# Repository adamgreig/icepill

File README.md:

# iCE Pill

Breakout board for iCE40UP5k with the STM32F411 "Black Pill" board.

This board breaks all the iCE40UP5k GPIO to PMOD headers, most of which are
also connected to Black Pill pins, allowing either the STM32 or the iCE40 to
drive each PMOD pin. The iCE40's SPI and configuration pins are connected to
the Black Pill, allowing the STM32 to program and control the iCE40.

The SPI and configuration pins are also exposed on the J8 and J9 pin headers,
allowing connection just to these signals and then all PMOD pins can be
exclusively used by the iCE40.

Two additional STM32 pins can be connected to the iCE40: PA8, which can be used
in its MCO or TIM1 CH1 alternate modes to generate a clock for the iCE40, and
PB10, which can be used to signal an interrupt from the iCE40. Zero-ohm
resistors are be fitted in R2 and R3 to connect these signals to PMOD pins
as well, and zero-ohm resistors can optionally be fitted in R7 and R8 to
connect PA9 and PB4 from the STM32 to the same PMOD pins. This configuration
means the iCE40 is always connected to PA8 (clock) and PB10 (interrupt), and
either those iCE40 pins can connect to the PMOD _or_ the STM32 pins PA9 and PB4
can connect to the PMOD instead.

R5 and R6 are present in case a 1.2V fixed LDO is not available and you need
to use an adjustable LDO. Otherwise, leave R5 not fitted and use a zero-ohm
resistor for R6 (the default).

The LED D1 is connected to the RGB0 _and_ RGB1 pins on the iCE40 to simplify
routing; it is recommended that only one pin is used at the same time when
driving the LED.

Pin 35 connects to PMOD 7 pin 8; this pin can be a PLL input to the iCE40. If
the PLL is in use at all (whether fed from pin 35 or any other signal), then
pin 35 cannot be used as a regular input.

| PMOD      | iCE40 | STM32 | Notes
|-----------|-------|-------|------
| P1.1      | 12    | PA12  |
| P1.2      | 11    | PA11  |
| P1.3      | 10    | PA10  |
| P1.4      | 9     | PA9   | Used for IRQ with PB10, PA9 disconnected by default
|           |       |       |
| P2.1      | 21    | PB5   |
| P2.2      | 20    | PB4   | Used for CLK with PA8, PB4 disconnected by default
| P2.3      | 19    | PB3   |
| P2.4      | 18    | PA15  |
|           |       |       |
| P3.1      | 28    | PB9   |
| P3.2      | 27    | PB8   |
| P3.3      | 26    | PB7   |
| P3.4      | 25    | PB6   |
|           |       |       |
| P4.1      | 44    | PA1   |
| P4.2      | 43    | PA0   |
| P4.3      | 42    |       |
| P4.4      | 38    | PC13  |
|           |       |       |
| P5.1      | 48    | PA5   |
| P5.2      | 47    | PA4   |
| P5.3      | 46    | PA3   |
| P5.4      | 45    | PA2   |
|           |       |       |
| P6.1      | 6     | PB1   |
| P6.2      | 4     | PB0   |
| P6.3      | 3     | PA7   |
| P6.4      | 2     | PA6   |
|           |       |       |
| P7.1      | 36    |       |
| P7.2      | 34    |       |
| P7.3      | 31    |       |
| P7.4      | 13    |       |
| P7.7      | 37    |       |
| P7.8      | 35    |       | If PLL active, can only be used as PLL input
| P7.9      | 32    |       |
| P7.10     | 23    |       |
|           |       |       |
|           | 14    | PB14  | SPI SO
|           | 15    | PB13  | SPI SCK
|           | 16    | PB12  | SPI CS
|           | 17    | PB15  | SPI SI
|           | 8     | PB2   | iCE40 CRESET
|           |       |       |
|           | 39    |       | LED on iCE40 RGB0 pin
|           | 40    |       | Connected to pin 39

Symbols and footprints copied from [agg-kicad]. This schematic and PCB design
are licensed under the Creative Commons [CC0 public domain dedication]. It is
provided with no warranty.

[agg-kicad]: https://github.com/adamgreig/agg-kicad
[CC0 public domain dedication]: https://creativecommons.org/publicdomain/zero/1.0/

## Revision History

### 1.0: 2020-11-08

* First revision.
* Errata:
    * None yet.

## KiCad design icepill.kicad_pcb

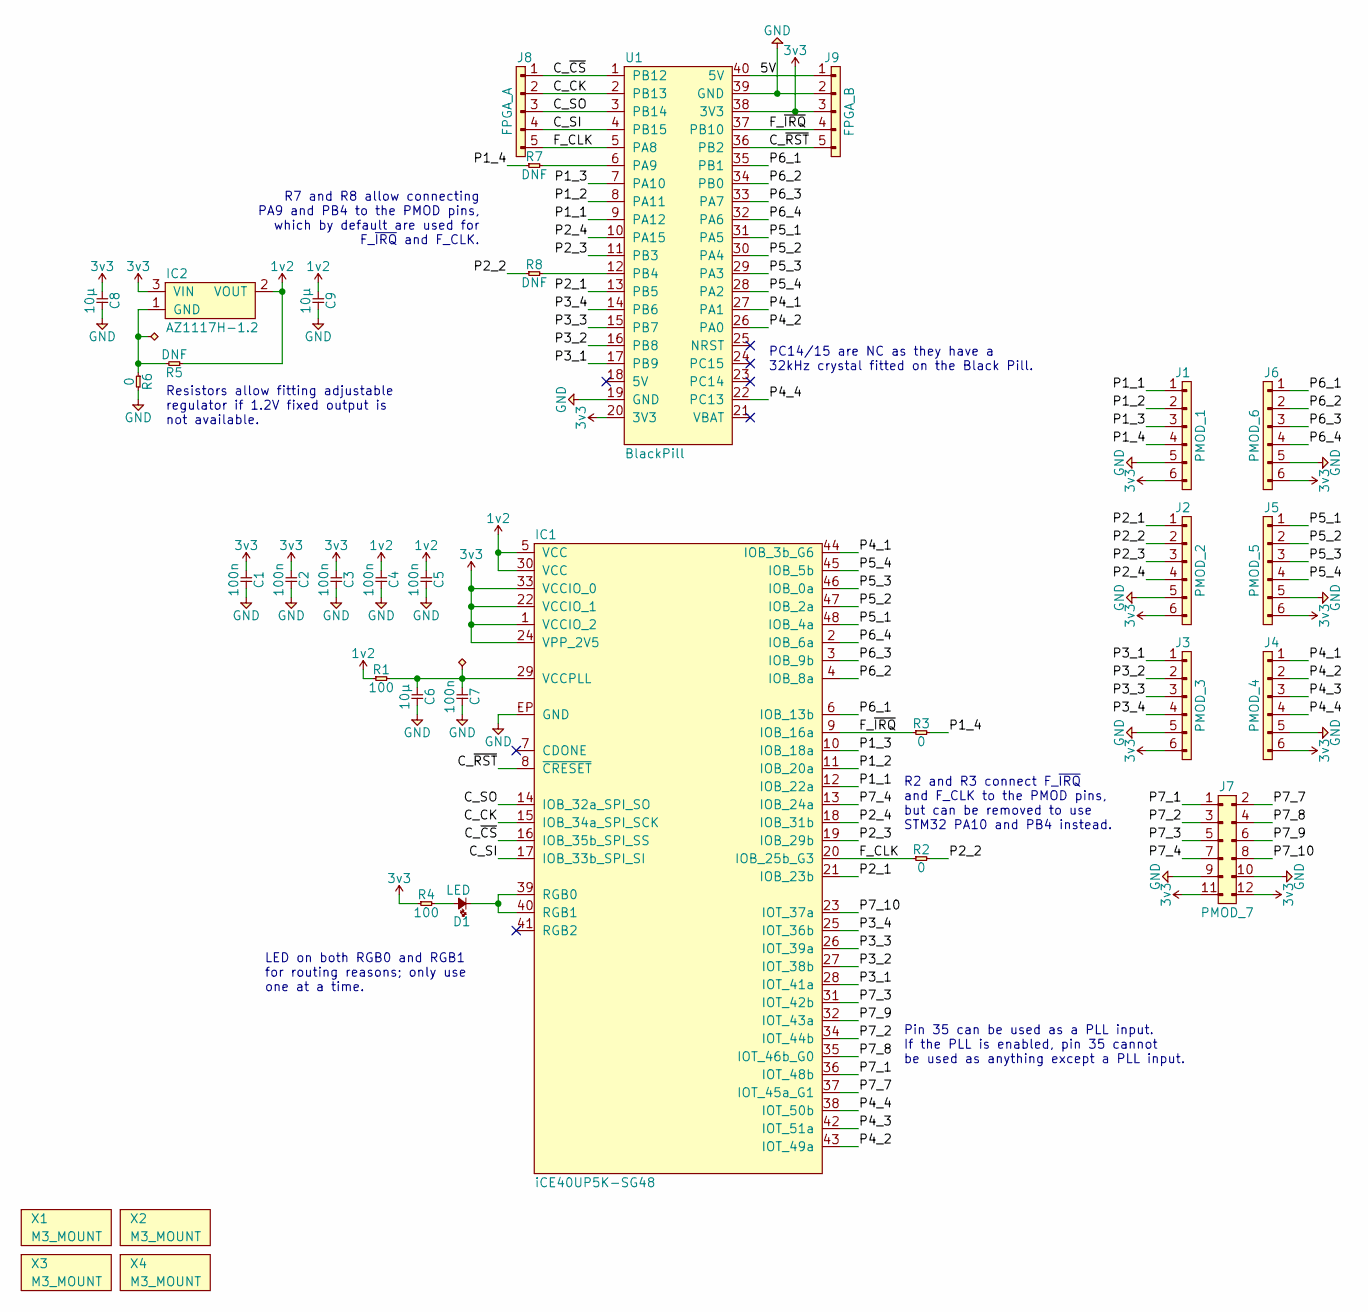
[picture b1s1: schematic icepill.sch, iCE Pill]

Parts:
C1, C2, C3, C4, C5, C7: 100n; 0603; Voltage 10
C6, C8, C9: 10µ; 0805; Voltage 10
D1: LED; 0603-LED
IC1: iCE40UP5K-SG48; Lattice-SG48; DigiKey 220-2212-1-ND
IC2: AZ1117H-1.2; SOT223
J1: PMOD_1; SIL-254P-06
J2: PMOD_2; SIL-254P-06
J3: PMOD_3; SIL-254P-06
J4: PMOD_4; SIL-254P-06
J5: PMOD_5; SIL-254P-06
J6: PMOD_6; SIL-254P-06
J7: PMOD_7; DIL-254P-12
J8: FPGA_A; SIL-254P-05
J9: FPGA_B; SIL-254P-05
R1, R4: 100; 0603
R2, R3, R6: 0; 0603
R5, R7, R8: DNF; 0603
U1: BlackPill
X1, X2, X3, X4: M3_MOUNT

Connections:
1v2: C4.1, C5.1, C9.1, IC1.5 (VCC), IC1.30 (VCC), IC2.2 (VOUT), R1.1, R5.1
3v3: C1.1, C2.1, C3.1, C8.1, IC1.1 (VCCIO_2), IC1.22 (VCCIO_1), IC1.24 (VPP_2V5), IC1.33 (VCCIO_0), IC2.3 (VIN), J1.6, J2.6, J3.6, J4.6, J5.6, J6.6, J7.11, J7.12, J9.3, R4.1, U1.20 (3V3), U1.38 (3V3)
/5V: J9.1, U1.40 (5V)
/C_CK: IC1.15 (IOB_34a_SPI_SCK), J8.2, U1.2 (PB13)
/C_SI: IC1.17 (IOB_33b_SPI_SI), J8.4, U1.4 (PB15)
/C_SO: IC1.14 (IOB_32a_SPI_SO), J8.3, U1.3 (PB14)
/C_~CS: IC1.16 (IOB_35b_SPI_SS), J8.1, U1.1 (PB12)
/C_~RST: IC1.8 (~CRESET), J9.5, U1.36 (PB2)
/F_CLK: IC1.20 (IOB_25b_G3), J8.5, R2.1, U1.5 (PA8)
/F_~IRQ: IC1.9 (IOB_16a), J9.4, R3.1, U1.37 (PB10)
/P1_1: IC1.12 (IOB_22a), J1.1, U1.9 (PA12)
/P1_2: IC1.11 (IOB_20a), J1.2, U1.8 (PA11)
/P1_3: IC1.10 (IOB_18a), J1.3, U1.7 (PA10)
/P1_4: J1.4, R3.2, R7.1
/P2_1: IC1.21 (IOB_23b), J2.1, U1.13 (PB5)
/P2_2: J2.2, R2.2, R8.1
/P2_3: IC1.19 (IOB_29b), J2.3, U1.11 (PB3)
/P2_4: IC1.18 (IOB_31b), J2.4, U1.10 (PA15)
/P3_1: IC1.28 (IOT_41a), J3.1, U1.17 (PB9)
/P3_2: IC1.27 (IOT_38b), J3.2, U1.16 (PB8)
/P3_3: IC1.26 (IOT_39a), J3.3, U1.15 (PB7)
/P3_4: IC1.25 (IOT_36b), J3.4, U1.14 (PB6)
/P4_1: IC1.44 (IOB_3b_G6), J4.1, U1.27 (PA1)
/P4_2: IC1.43 (IOT_49a), J4.2, U1.26 (PA0)
/P4_3: IC1.42 (IOT_51a), J4.3
/P4_4: IC1.38 (IOT_50b), J4.4, U1.22 (PC13)
/P5_1: IC1.48 (IOB_4a), J5.1, U1.31 (PA5)
/P5_2: IC1.47 (IOB_2a), J5.2, U1.30 (PA4)
/P5_3: IC1.46 (IOB_0a), J5.3, U1.29 (PA3)
/P5_4: IC1.45 (IOB_5b), J5.4, U1.28 (PA2)
/P6_1: IC1.6 (IOB_13b), J6.1, U1.35 (PB1)
/P6_2: IC1.4 (IOB_8a), J6.2, U1.34 (PB0)
/P6_3: IC1.3 (IOB_9b), J6.3, U1.33 (PA7)
/P6_4: IC1.2 (IOB_6a), J6.4, U1.32 (PA6)
/P7_1: IC1.36 (IOT_48b), J7.1
/P7_2: IC1.34 (IOT_44b), J7.3
/P7_3: IC1.31 (IOT_42b), J7.5
/P7_4: IC1.13 (IOB_24a), J7.7
/P7_7: IC1.37 (IOT_45a_G1), J7.2
/P7_8: IC1.35 (IOT_46b_G0), J7.4
/P7_9: IC1.32 (IOT_43a), J7.6
/P7_10: IC1.23 (IOT_37a), J7.8
GND: C1.2, C2.2, C3.2, C4.2, C5.2, C6.2, C7.2, C8.2, C9.2, IC1.EP (GND), J1.5, J2.5, J3.5, J4.5, J5.5, J6.5, J7.9, J7.10, J9.2, R6.2, U1.19 (GND), U1.39 (GND)
unnamed: C6.1, C7.1, IC1.29 (VCCPLL), R1.2
unnamed: D1.1, IC1.39 (RGB0), IC1.40 (RGB1)
unnamed: D1.2, R4.2
unnamed: IC2.1 (GND), R5.2, R6.1
unnamed: R7.2, U1.6 (PA9)
unnamed: R8.2, U1.12 (PB4)

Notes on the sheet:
Pin 35 can be used as a PLL input. If the PLL is enabled, pin 35 cannot be used as anything except a PLL input.
R7 and R8 allow connecting PA9 and PB4 to the PMOD pins, which by default are used for F_~IRQ~ and F_CLK.
LED on both RGB0 and RGB1 for routing reasons; only use one at a time.
Resistors allow fitting adjustable regulator if 1.2V fixed output is not available.
PC14/15 are NC as they have a 32kHz crystal fitted on the Black Pill.
R2 and R3 connect F_~IRQ~ and F_CLK to the PMOD pins, but can be removed to use STM32 PA10 and PB4 instead.

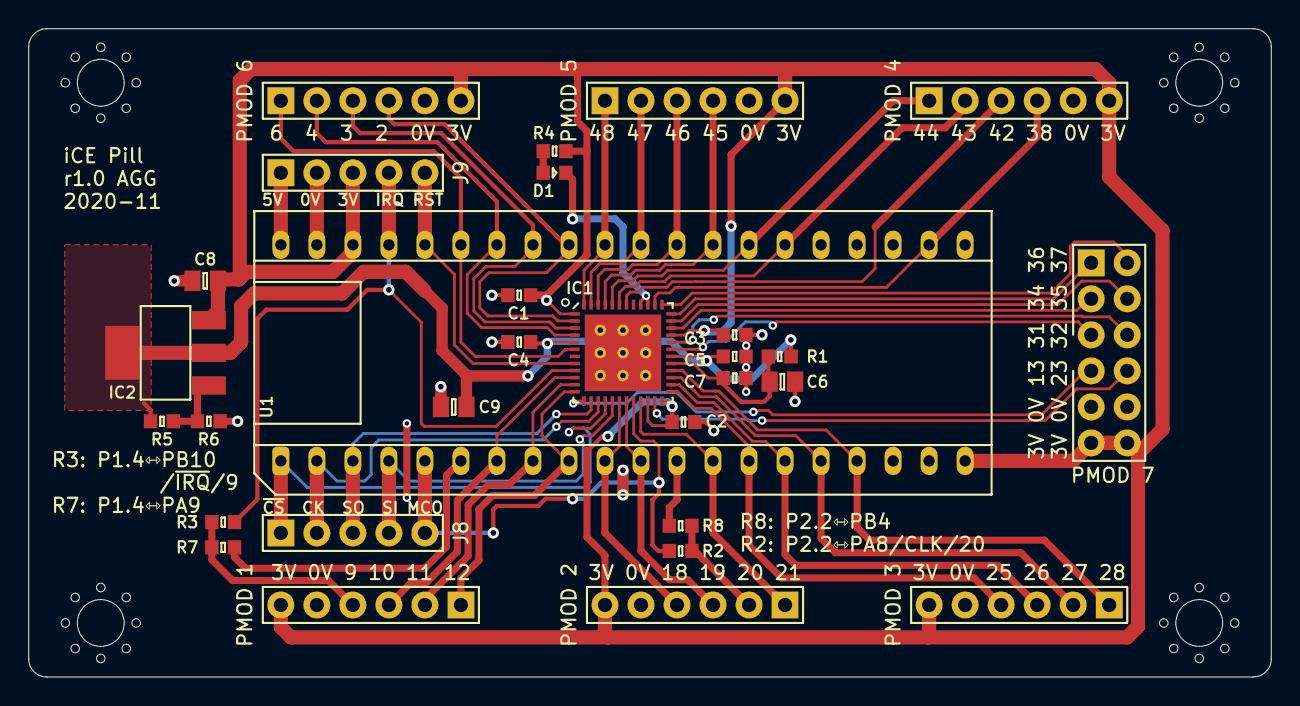
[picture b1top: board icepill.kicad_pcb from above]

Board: 2 copper layers, 87.6 x 45.7 mm, 34 parts (0 on the bottom side), 49 nets.

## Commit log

2020-11-08 Initial commit. First revision routed.
2020-11-08 Add README
2020-11-08 Add power flags to PLL supply and LDO GND
2020-11-08 Fix PB0/PB10 typo in README
2020-11-08 Address first revision feedback.
    * MCO from STM32 now routes to GB3 (pin 20), a global input.
    * Consequently F_CLK is now present at PMOD2.2.
    * PC14 and PC15 no longer connected as they have an LSE on the Black Pill.
    * F_IRQ moved to PMOD1.4.
    * 0R resistors for selecting IRQ and CLK presence at PMODs changed to
    allow either STM32 or iCE40 to drive the PMOD pin, while the iCE40
2020-11-08 Add pinout table to README, update render.
2020-11-08 Update silk for R2/3/7/8
2020-11-08 Update render

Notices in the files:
icepill.kicad_pcb:
License: CC0
